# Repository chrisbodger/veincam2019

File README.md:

VeinCam is an educational tool for vein visualisation. It uses near infrared (nIR) light and a camera to stream a real-time image where veins can be easily seen. It is an open-source, build-it-yourself device so anyone who finds it useful will be able to construct it. There is a how-to guide of what materials to buy, how to put them together and the software to upload to get it all working.

This is the repository for the continuation of the VeinCam Project as an ANU Engineering Captone Project in 2019. The repository for the previous work can be found [HERE](https://www.github.com/chrisbodger/veincam). This repository will be used to delineate and document the progress made this semester, in what is to be the next chapter of this exciting project. 

---
# Table Of Contents
1. [Project Goals](#1-project-goals)
2. [Feedback](#2-feedback)
3. [Project Updates](#3-project-updates)
4. [Concept of Operations](#4-concept-of-operations)
5. [Meeting Minutes](#5-meeting-minutes)
6. [Decision Log](#6-decision-log)

---
# 1. Project Goals
There are 3 goals we wish to achieve this semester:

1. Develop a set of hardware requirements that are suitable for the VeinCam Project.
2. Optimise the software to run more efficiently.
3. Compile procurement options to develop kits to be able to be sold onto those who wish to build a VeinCam for themselves.

# 2. Feedback
A feedback form has been created for the interest of our stakeholders, should they wish to pass on any changes or improvements they believe to be prudent. The form can be found [here](https://goo.gl/forms/8cw5eWdaOY5C1jBo1).

# 3. Project Updates
### Week 11 - 22/05/2019

### School Visit
The team showcased VeinCam to Gungahlin College and gained insightful feedback into how VeinCam could be used in a secondary school environment. A summary of the visit is available [here](Administration/Communications/Gungahlin-College-Visit-210519.md).

#### Hardware
Final prototypes of the VeinCam enclosure completed, along with some PCB changes to better utilise onboard LEDs. Pricing for enclosure, along with final bill of materials determined. 

### Software

This week was spent getting all documenation up to date. Colour functionality added to MJPEG steam, fixed banding effects and scaling to better suit mobile and tablet users. 

### Previous Updates
More specific updates regarding each sub-team are available in the sub-team work diaries. These can be found in the [Hardware](/Hardware/HardwareDiary.md) and [Software](/Software/SoftwareDiary.md) folders, as well as team [Decision Logs](/Administration/Project/Decision-Log.md) are other locations for progress notes, should they not be located on this page.

# 4. Concept of Operations
Our Concept of Operations has been signed off by all parties involved. 

The [Concept of Operations](Administration/Project/CONOPS.md) document can be found in our repository.

# 5. Meeting Minutes
The team regularly meet to formally discuss the project's progress, as well as through other communication channels. the minutes from the formal discussions can be found in the [Meeting Minutes](Administration/meeting-minutes/) directory.

# 6. Decision Log
Major decisions that affect the majority or all of the project's future work and/or operations can be found in the [Decision Log](Administration/Project/Decision-Log.md/).

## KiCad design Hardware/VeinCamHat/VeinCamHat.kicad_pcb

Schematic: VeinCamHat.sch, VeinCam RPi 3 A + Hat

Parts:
D1: GREEN LED; LED_0805_2012Metric
D2: RED LED; LED_0805_2012Metric
D3, D4, D5, D6, D7, D8: SFH7252
H1, H2, H3, H4: MountingHole; MountingHole_2.7mm_M2.5
J1: Raspberry_Pi_2_3; PinSocket_2x20_P2.54mm_Vertical
Q1: NTJD4001N; SOT-363_SC-70-6
R1: 1K; R_0603_1608Metric
R2: 1K5; R_0603_1608Metric
R3, R4, R5, R6: 3R3; R_0603_1608Metric
R7, R8: 10K; R_0603_1608Metric
TP1: Camera Outline; PiCamera

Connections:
+3V3: D2.2 (A), J1.17 (3V3)
+5V: J1.2 (5V), J1.4 (5V), R3.2, R4.2, R5.2, R6.2
/LED_850: J1.12 (GPIO18/PWM0), Q1.2, R7.1
/LED_940: J1.33 (PWM1/GPIO13), Q1.5, R8.1
/LED_READY: J1.37 (GPIO26), R1.2
/nLED_BOOT: J1.35 (GPIO19/MISO1), R2.1
GND: D1.1 (K), J1.6 (GND), J1.9 (GND), J1.14 (GND), J1.20 (GND), J1.25 (GND), J1.30 (GND), J1.34 (GND), J1.39 (GND), Q1.1, Q1.4, R7.2, R8.2
unnamed: D1.2 (A), R1.1
unnamed: D2.1 (K), R2.2
unnamed: D3.1 (K2), D5.2 (A2)
unnamed: D3.2 (A2), R3.1
unnamed: D3.3 (K1), D5.4 (A1)
unnamed: D3.4 (A1), R4.1
unnamed: D4.1 (K2), D6.2 (A2)
unnamed: D4.2 (A2), R5.1
unnamed: D4.3 (K1), D6.4 (A1)
unnamed: D4.4 (A1), R6.1
unnamed: D5.1 (K2), D7.2 (A2)
unnamed: D5.3 (K1), D7.4 (A1)
unnamed: D6.1 (K2), D8.2 (A2)
unnamed: D6.3 (K1), D8.4 (A1)
unnamed: D7.1 (K2), D8.1 (K2), Q1.3
unnamed: D7.3 (K1), D8.3 (K1), Q1.6

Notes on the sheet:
RPi Connector
M2.5
IR LED's
2->1 940nm 3->4 850nm
Status LEDs
For Camera

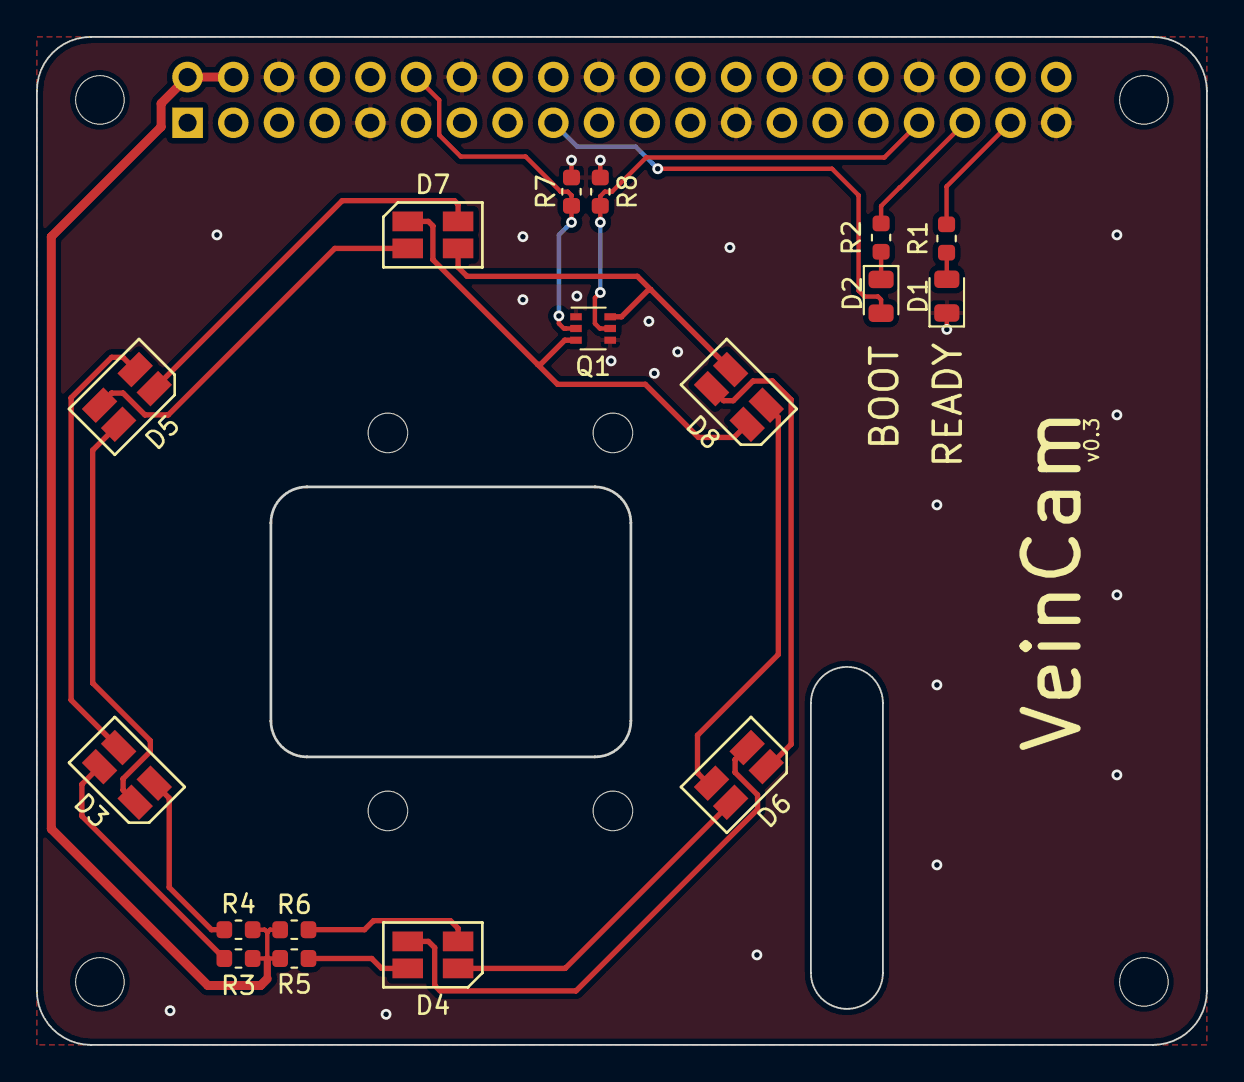
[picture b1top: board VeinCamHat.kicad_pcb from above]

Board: 2 copper layers, 65.0 x 56.0 mm, 23 parts (1 on the bottom side), 23 nets.

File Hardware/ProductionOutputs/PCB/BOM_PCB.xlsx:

Item | Qty | Reference(s) | Value | LibPart | Footprint | Supplier Link
1 | 1 | D1 | GREEN LED | Device:LED | LED_SMD:LED_0805_2012Metric | https://lcsc.com/product-detail/Light-Emitting-Diodes-LED_LE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
2 | 1 | D2 | RED LED | Device:LED | LED_SMD:LED_0805_2012Metric | https://lcsc.com/product-detail/Light-Emitting-Diodes-LED_re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
3 | 6 | D3, D4, D5, D6, D7, D8 | SFH7252 | VeinCam_Symbols:SFH7252 | VeinCam_Footprints:SFH7252 | https://au.mouser.com/ProductDetail/OSRAM-Opto-Semiconductor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
5 | 1 | J1 | Raspberry_Pi_2_3 | Connector:Raspberry_Pi_2_3 | Connector_PinSocket_2.54mm:PinSocket_2x20_P2.54mm_Vertical | https://lcsc.com/product-detail/Others_2685Y-220CNG1SNA01_C3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
6 | 1 | Q1 | NTJD4001N | VeinCam_Symbols:NTJD4001N | Package_TO_SOT_SMD:SOT-363_SC-70-6 | https://lcsc.com/product-detail/MOSFET_ON-Semicon_NTJD4001NT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
7 | 1 | R1 | 1K | Device:R | Resistor_SMD:R_0603_1608Metric | https://lcsc.com/product-detail/Others_ResistorToday-ETCR060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
8 | 1 | R2 | 1K5 | Device:R | Resistor_SMD:R_0603_1608Metric | https://lcsc.com/product-detail/Chip-Resistor-Surface-Mount_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
9 | 2 | R7, R8 | 10K | Device:R | Resistor_SMD:R_0603_1608Metric | https://lcsc.com/product-detail/Chip-Resistor-Surface-Mount_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
10 | 1 | RN1 | R_Pack04 | Device:R_Pack04 | Resistor_SMD:R_Array_Convex_4x0603 | https://au.mouser.com/ProductDetail/Bourns/CAY16-3R0J4LF?qs=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
 |  |  |  |  |  | Depending on specific LEDs, R1 and R2 may need to be changed to set brightness 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
 |  |  |  |  |  | Suggest purchasing below to allow for swapping out of parts if required
 |  |  |  |  |  | https://lcsc.com/product-detail/Chip-Resistor-Surface-Mount_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

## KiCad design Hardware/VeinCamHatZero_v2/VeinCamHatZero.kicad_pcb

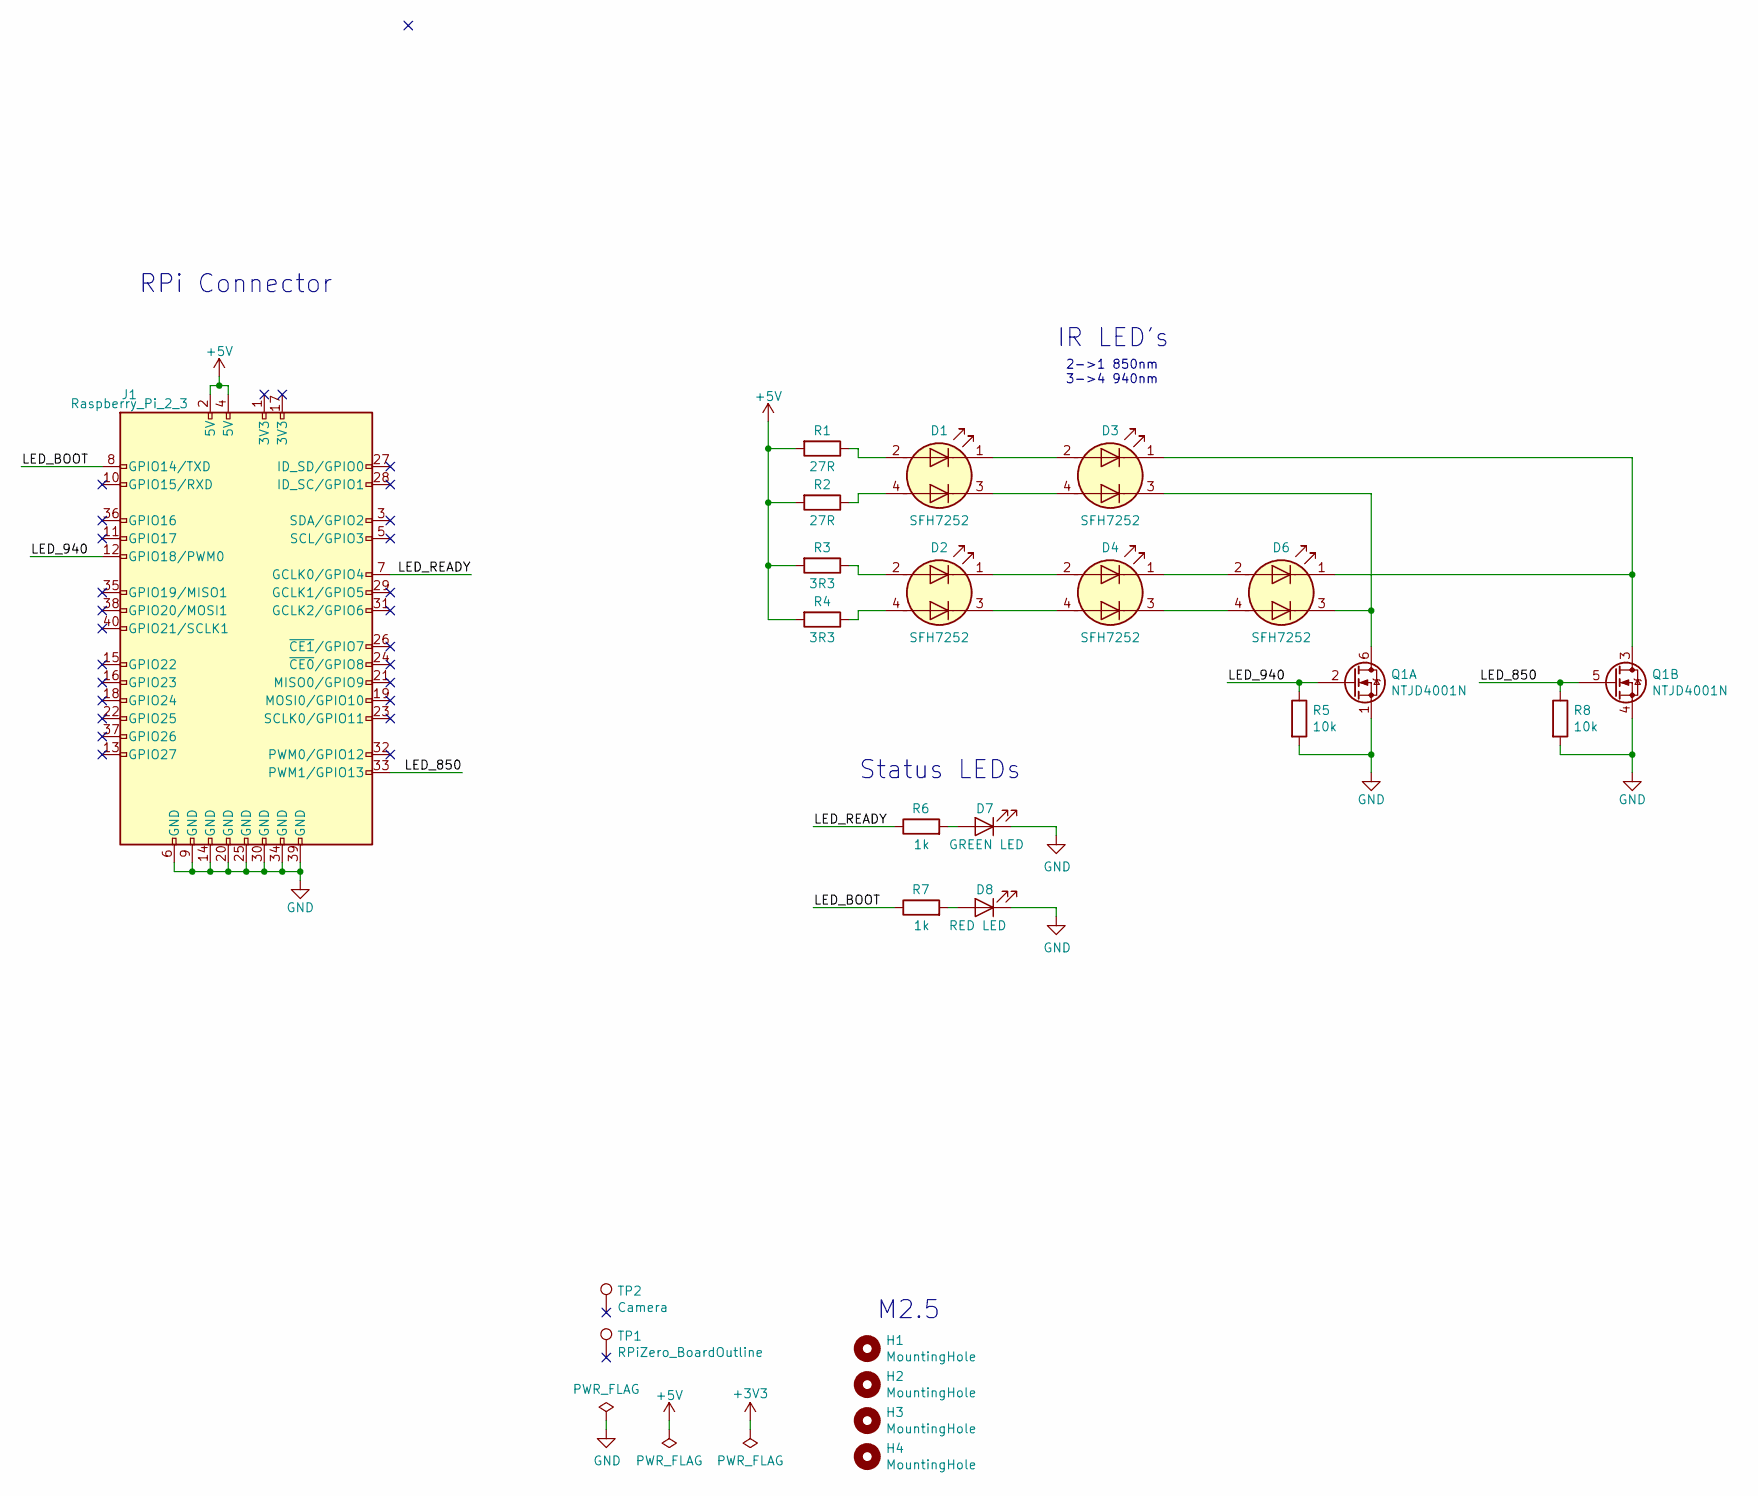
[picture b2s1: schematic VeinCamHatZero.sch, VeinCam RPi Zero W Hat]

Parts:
D1, D2, D3, D4, D6: SFH7252
D7: GREEN LED; LED_0805_2012Metric
D8: RED LED; LED_0805_2012Metric
H1, H2, H3, H4: MountingHole; MountingHole_2.7mm_M2.5
J1: Raspberry_Pi_2_3; PinSocket_2x20_P2.54mm_Vertical
Q1: NTJD4001N; SOT-363_SC-70-6
R1, R2: 27R; R_0603_1608Metric
R3, R4: 3R3; R_0603_1608Metric
R5, R8: 10k; R_0603_1608Metric
R6, R7: 1k; R_0603_1608Metric
TP1: RPiZero_BoardOutline; PIRHAT_ZERO_noCutouts
TP2: Camera; PiCamera

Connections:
+5V: J1.2 (5V), J1.4 (5V), R1.2, R2.2, R3.2, R4.2
/LED_850: J1.33 (PWM1/GPIO13), Q1.5 (G), R8.1
/LED_940: J1.12 (GPIO18/PWM0), Q1.2 (G), R5.1
/LED_BOOT: J1.8 (GPIO14/TXD), R7.1
/LED_READY: J1.7 (GCLK0/GPIO4), R6.1
GND: D7.1 (K), D8.1 (K), J1.6 (GND), J1.9 (GND), J1.14 (GND), J1.20 (GND), J1.25 (GND), J1.30 (GND), J1.34 (GND), J1.39 (GND), Q1.1 (S), Q1.4 (S), R5.2, R8.2
unnamed: D1.1 (K2), D3.2 (A2)
unnamed: D1.2 (A2), R1.1
unnamed: D1.3 (K1), D3.4 (A1)
unnamed: D1.4 (A1), R2.1
unnamed: D2.1 (K2), D4.2 (A2)
unnamed: D2.2 (A2), R3.1
unnamed: D2.3 (K1), D4.4 (A1)
unnamed: D2.4 (A1), R4.1
unnamed: D3.1 (K2), D6.1 (K2), Q1.3 (D)
unnamed: D3.3 (K1), D6.3 (K1), Q1.6 (D)
unnamed: D4.1 (K2), D6.2 (A2)
unnamed: D4.3 (K1), D6.4 (A1)
unnamed: D7.2 (A), R6.2
unnamed: D8.2 (A), R7.2

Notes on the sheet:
RPi Connector
M2.5
IR LED's
2->1 850nm 3->4 940nm
Status LEDs

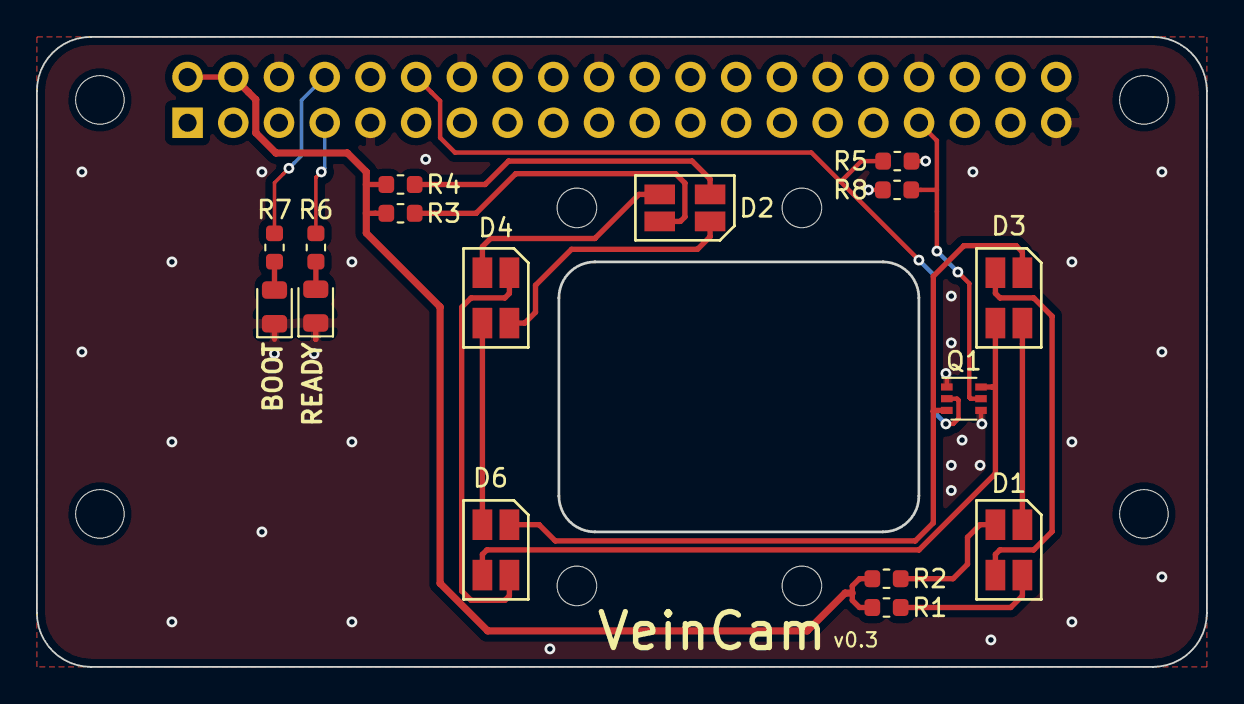
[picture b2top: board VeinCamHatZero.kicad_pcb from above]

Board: 2 copper layers, 65.0 x 35.0 mm, 22 parts (1 on the bottom side), 20 nets.

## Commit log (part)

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2019-03-06 Create README.md
    Initial Commit of Repo
2019-03-08 Initial Code Upload
2019-03-08 Software folder Rearrange
2019-03-08 Initial draft of CONOPS.md
2019-03-08 Small edits to CONOPS.md
2019-03-09 Meeting minutes for 9/3/19
    to be filled out by TJ
2019-03-10 Resource Uploads
2019-03-10 Create Requirements
    Revised requirements from last year. Ideally to be reviewed by Chris and co.
2019-03-10 Update Requirements.md
    Revised requirements from last year. Ideally to be reviewed by Chris and co.
2019-03-11 Minutes adjustment
2019-03-11 Administration organisation
2019-03-12 Create week-3
2019-03-12 Rename week-3 to week-3.md
2019-03-12 Rename week-3.md to Tuesday Week 3 12-03-19.md
2019-03-12 Create Tuesday Week 3 12-03-19
2019-03-12 Added VeinCamHat PCA files
2019-03-13 Hardware Updates
2019-03-13 Schematic for RPiZero hat completed, BOM generation and Estimated Financials completed.
2019-03-14 ConOps Draft v1.1
    Updated where appropriate using comparison of previous ConOps.
    Sections to complete clearly marked. TBC by 10am 15/03 by A.O
2019-03-14 ConOps v.1.1
    Updated ConOps, things left to do TBC by 15/03 by A.O
2019-03-14 Added SBC Comparison
2019-03-14 Started landing page rewrite
2019-03-16 Landing Page Update
2019-03-17 Added comments about pricing being determined to README.md
2019-03-17 Fix link in README.md
2019-03-17 updated software audit 1
2019-03-17 Couple Spelling errors
2019-03-17 Added Shadow Team Members to CONOPS
2019-03-17 ConOps v1.2
2019-03-17 Landing page images
2019-03-18 Added HW Requirements and RPI3A renders
2019-03-18 Added Visio PDF
2019-03-18 Added Matlab Testing File
2019-03-18 Added Software Diary
2019-03-18 Laid out VeinCamHatZero and added IR LED footprint/model
2019-03-18 Added footprints for VeinCamHat and begun layout
2019-03-18 Changes to renders
2019-03-19 Create Tuesday Week 4 19-03-19
2019-03-19 Rename Tuesday Week 4 19-03-19 to Tuesday Week 4 19-03-19.md
2019-03-19 Changed plans for VeinCam Plus, both boards laid out
2019-03-19 More Hardware changes, both boards complete
2019-03-19 updates to renders
2019-03-22 final board changes, gerbers generated
2019-03-22 Finished boards, v0.2 gerbers zipped and sent off to fab
2019-03-23 found possible IR filter suppliers
2019-03-23 added potential suppliers for IR filter
2019-03-23 Rename Action Items from Audit 1 Feedback.md to Feedback and Action Items from Audit 1 Feedback.md
2019-03-23 Rename Feedback and Action Items from Audit 1 Feedback.md to Feedback and Action Items from Audit 1.md
2019-03-26 Update Tuesday Week 5 26-03-19.md
    Updated software minutes
2019-03-26 stuff
2019-03-27 app.py testing
2019-03-28 client correspondence file addition
2019-03-28 Added 3d Models + hardware readme
2019-03-29 Updated software diary from todays work
2019-03-29 Create External-Communications.md
    Created new file for external communications with educators, etc. Will place client communications in same folder.
2019-03-29 Folder rearrange
2019-04-01 Update CONOPS.md
    Updated WBS, Project vision, updated document version for Audit 2
2019-04-01 Updated case design and spacers
2019-04-01 Updated HW Diary
2019-04-01 Audit 1 Update Archive
2019-04-01 update readme with HW updates
2019-04-01 Updated software and ConOps sections
2019-04-01 Update client correspondence
2019-04-01 Rename Commercial_Viability.mb to Commercial_Viability.md
2019-04-01 updated schematics
2019-04-02 Changed pricing details and added links for mounting hardware.
2019-04-03 updated software diaries
2019-04-07 Create LICENSE
2019-04-07 changed logo direction on veincam, added licencing document
2019-04-08 Added v2 of the VeinCam Zero board
2019-04-11 VC zero changes
2019-04-19 More schematic / PCB changes
2019-04-22 Lots of Software Cleaning (work in progress)
2019-04-23 Josh can't read datasheets correctly
2019-04-23 Rename bootstrap.css to css/bootstrap.css
2019-04-23 Rename js/readme.md to js/modules/readme.md
2019-04-23 Updated HTML files
2019-04-23 updated html
2019-04-23 updated font
2019-04-23 copied clients html code
2019-04-23 reversed
2019-04-23 fonts
2019-04-23 font 2
2019-04-23 font3
2019-04-23 font4
2019-04-23 learned how to use girkraken so i didnt have to commit a billion times. Updated webpage.
2019-04-23 piopencv big cleanup into 1 file + app.py fixes LED pins fixed in app.py included launch file with new boot LED write
2019-04-23 Added python openCV testing file and image
2019-04-24 quick syntax fix camera_piopencv
2019-04-29 HTML
2019-04-29 added actionable items
2019-04-30 delayed HW diary commit
2019-04-30 Software Diary update to current (30.04.2019)
2019-04-30 added HW comments to Ben's message
2019-04-30 Added DXFs of acrylic plates
2019-05-12 Added Assembly Instructions and updated pricing
2019-05-12 small app.py clean
2019-05-12 added decision to kill veinCam zero
2019-05-12 updated hardware progress
2019-05-13 Uploaded images from Bonython Primary School trip
2019-05-13 Rename Administration/Poster Presentation Notes.md to Administration/Poster/Poster Presentation Notes.md
2019-05-13 Rename Commercial_Viability.md to Commercial-Viability.md
2019-05-13 Added YUV and MJPEG Colour functionality and beeg UI QOL fixes, especially image window
2019-05-13 Folder Name Change for Repo Cleanliness
2019-05-13 Changes Testing Images Folder Updated Software Diaries
2019-05-13 Client Feedback Update - Software
2019-05-13 Small Decision Log Fix will update tomorrow (15/05/19)
2019-05-13 Added new draft High Level
2019-05-14 updated commercial viability document
2019-05-15 added HW stuff to handover document
2019-05-18 Create CNAME
2019-05-18 Update CNAME
2019-05-20 updating hardware things
2019-05-20 removing old files
2019-05-20 Software Diary Completion
2019-05-21 Added software assembly instructions
2019-05-21 app.py Final Clean
2019-05-21 Small app.py syntax fixes
2019-05-22 Handover Document Software Update
2019-05-22 Created and Finished Software README, Small app.py fix
2019-05-22 small software fix
2019-05-22 Added Custom Loading Gifs for Future Use
2019-05-22 Edit software readme name
2019-05-26 Updates to board and generation of final production outputs
2019-05-26 added more render photos
2020-07-16 Bump lodash from 4.17.11 to 4.17.19
    Bumps [lodash](https://github.com/lodash/lodash) from 4.17.11 to 4.17.19.
    - [Release notes](https://github.com/lodash/lodash/releases)
    - [Commits](https://github.com/lodash/lodash/compare/4.17.11...4.17.19)
2020-09-04 Bump node-sass from 4.11.0 to 4.14.1
    Bumps [node-sass](https://github.com/sass/node-sass) from 4.11.0 to 4.14.1.
    - [Release notes](https://github.com/sass/node-sass/releases)
    - [Changelog](https://github.com/sass/node-sass/blob/master/CHANGELOG.md)
    - [Commits](https://github.com/sass/node-sass/compare/v4.11.0...v4.14.1)
2020-09-04 Bump lodash.mergewith from 4.6.1 to 4.6.2
    Bumps [lodash.mergewith](https://github.com/lodash/lodash) from 4.6.1 to 4.6.2.
    - [Release notes](https://github.com/lodash/lodash/releases)
    - [Commits](https://github.com/lodash/lodash/commits)
2020-12-11 Bump ini from 1.3.5 to 1.3.7
    Bumps [ini](https://github.com/isaacs/ini) from 1.3.5 to 1.3.7.
    - [Release notes](https://github.com/isaacs/ini/releases)
    - [Commits](https://github.com/isaacs/ini/compare/v1.3.5...v1.3.7)
2021-03-30 Bump y18n from 3.2.1 to 3.2.2
    Bumps [y18n](https://github.com/yargs/y18n) from 3.2.1 to 3.2.2.
    - [Release notes](https://github.com/yargs/y18n/releases)
    - [Changelog](https://github.com/yargs/y18n/blob/master/CHANGELOG.md)
    - [Commits](https://github.com/yargs/y18n/commits)
2021-05-08 Bump lodash from 4.17.11 to 4.17.21
    Bumps [lodash](https://github.com/lodash/lodash) from 4.17.11 to 4.17.21.
    - [Release notes](https://github.com/lodash/lodash/releases)
    - [Commits](https://github.com/lodash/lodash/compare/4.17.11...4.17.21)
2021-05-10 Bump hosted-git-info from 2.7.1 to 2.8.9
    Bumps [hosted-git-info](https://github.com/npm/hosted-git-info) from 2.7.1 to 2.8.9.
    - [Release notes](https://github.com/npm/hosted-git-info/releases)
    - [Changelog](https://github.com/npm/hosted-git-info/blob/v2.8.9/CHANGELOG.md)
    - [Commits](https://github.com/npm/hosted-git-info/compare/v2.7.1...v2.8.9)
2021-05-25 Bump browserslist from 4.4.1 to 4.16.6
    Bumps [browserslist](https://github.com/browserslist/browserslist) from 4.4.1 to 4.16.6.
    - [Release notes](https://github.com/browserslist/browserslist/releases)
    - [Changelog](https://github.com/browserslist/browserslist/blob/main/CHANGELOG.md)
    - [Commits](https://github.com/browserslist/browserslist/compare/4.4.1...4.16.6)
2021-06-15 Bump postcss from 7.0.14 to 7.0.36
    Bumps [postcss](https://github.com/postcss/postcss) from 7.0.14 to 7.0.36.
    - [Release notes](https://github.com/postcss/postcss/releases)
    - [Changelog](https://github.com/postcss/postcss/blob/main/CHANGELOG.md)
    - [Commits](https://github.com/postcss/postcss/compare/7.0.14...7.0.36)
    ---
    updated-dependencies:
2021-08-04 Bump tar from 2.2.1 to 2.2.2
    Bumps [tar](https://github.com/npm/node-tar) from 2.2.1 to 2.2.2.
    - [Release notes](https://github.com/npm/node-tar/releases)
    - [Changelog](https://github.com/npm/node-tar/blob/main/CHANGELOG.md)
    - [Commits](https://github.com/npm/node-tar/compare/v2.2.1...v2.2.2)
    ---
    updated-dependencies:
2021-08-10 Bump path-parse from 1.0.6 to 1.0.7
    Bumps [path-parse](https://github.com/jbgutierrez/path-parse) from 1.0.6 to 1.0.7.
    - [Release notes](https://github.com/jbgutierrez/path-parse/releases)
    - [Commits](https://github.com/jbgutierrez/path-parse/commits/v1.0.7)
    ---
    updated-dependencies:
    - dependency-name: path-parse
2022-01-13 Bump follow-redirects from 1.7.0 to 1.14.7
    Bumps [follow-redirects](https://github.com/follow-redirects/follow-redirects) from 1.7.0 to 1.14.7.
    - [Release notes](https://github.com/follow-redirects/follow-redirects/releases)
    - [Commits](https://github.com/follow-redirects/follow-redirects/compare/v1.7.0...v1.14.7)
    ---
    updated-dependencies:
    - dependency-name: follow-redirects
2022-02-11 Bump ajv from 6.9.1 to 6.12.6
    Bumps [ajv](https://github.com/ajv-validator/ajv) from 6.9.1 to 6.12.6.
    - [Release notes](https://github.com/ajv-validator/ajv/releases)
    - [Commits](https://github.com/ajv-validator/ajv/compare/v6.9.1...v6.12.6)
    ---
    updated-dependencies:
    - dependency-name: ajv
2022-02-12 Bump follow-redirects from 1.7.0 to 1.14.8
    Bumps [follow-redirects](https://github.com/follow-redirects/follow-redirects) from 1.7.0 to 1.14.8.
    - [Release notes](https://github.com/follow-redirects/follow-redirects/releases)
    - [Commits](https://github.com/follow-redirects/follow-redirects/compare/v1.7.0...v1.14.8)
    ---
    updated-dependencies:
    - dependency-name: follow-redirects
2022-06-27 Bump copy-props from 2.0.4 to 2.0.5
    Bumps [copy-props](https://github.com/gulpjs/copy-props) from 2.0.4 to 2.0.5.
    - [Release notes](https://github.com/gulpjs/copy-props/releases)
    - [Changelog](https://github.com/gulpjs/copy-props/blob/master/CHANGELOG.md)
    - [Commits](https://github.com/gulpjs/copy-props/compare/2.0.4...2.0.5)
    ---
    updated-dependencies:
2022-11-22 Bump engine.io and browser-sync
    Bumps [engine.io](https://github.com/socketio/engine.io) to 6.2.1 and updates ancestor dependency [browser-sync](https://github.com/BrowserSync/browser-sync). These dependencies need to be updated to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
    Updates `engine.io` from 3.2.1 to 6.2.1
    - [Release notes](https://github.com/socketio/engine.io/releases)
    - [Changelog](https://github.com/socketio/engine.io/blob/main/CHANGELOG.md)
    - [Commits](https://github.com/socketio/engine.io/compare/3.2.1...6.2.1)
    Updates `browser-sync` from 2.26.3 to 2.27.10
